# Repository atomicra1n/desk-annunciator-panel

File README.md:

# Desk Annunciator Panel

A smaller version of alarm panels found in Main Control Rooms of Nuclear Power Plants. Has 12 backlit alarm tiles, a seven segment display (8 digits) and ACK, RESET and TEST buttons. It is controlled by a Raspberry Pi Pico WH and shows live radiation readings from my [Wi-Fi Geiger Counter](https://github.com/atomicra1n/wifi-geiger-counter) which I made in Week 1 of Half Life. The alarm tiles light up when a problem occurs to notify me and play a sound.

## Features

- 12 alarm tiles with LEDs of three colors, red for critical alerts, yellow for warnings and white for reminders and general info.
- Proper annunciator sequence, new alarm flashes fast and creates sound, ACK makes the flashing steady and when condition is cleared it flashes slowly until RESET is pressed after which it stops being lit.
- TEST button lights up all tiles
- Seven segment display with 8 digits showing CPM and radiation levels in microSieverts/h from my Geiger project
- Demo mode for simulating alarms
- Fully through-hole with no SMD soldering and no screws needed for the enclosure

## Motivation

I've always loved nuclear energy and worked on many projects related to it. Annunciators are a particularly cool part of each NPP MCR and I thought having one at home would be really cool. Perhaps I can add a SCRAM button one day!

## Functionality

- The RPi Pico WH connects to Wi-Fi and checks the Geiger Counter's /api/data endpoint every 5 seconds to get the CPM, uSv/h, voltage status, counts and Wi-Fi signal
- Two shift registers drive the 12 tile LEDs. They run at 3.3V, and turn on yellow and red LEDs with a LOW output.
- White LEDs need 2.9V which is too close to 3.3V to work well, so they run from 5V via 2N3904 transistors. This means their logic is flipped.
- The MAX7219 display module needs 3.5V for a HIGH logic, yet our RPi only outputs 3.3V, so I made level shifters from three 2N3904 transistors. The signal is inverted, so the firmware must also send it inverted.
- The speaker is driven by another 2N3904 with a 47 ohm resistor and a flyback diode.
- Buttons go straight to the RPi Pico.

### Tiles

Red tiles: RAD HIGH, RAD HI-HI, HV FAULT, TUBE FAIL
Yellow tiles: RATE RISE, COMM LOST, WIFI WEAK, API ERROR
White tiles: WK REVIEWS, WK LESSONS, ANKI DUE, RAIN TODAY

I study Japanese and use many services to learn Kanji, vocabulary and grammar every day. As such, for the white tiles, I added tiles to notify me when I need to do some work on these services (WaniKani and Anki). However, as it would be a bit trickier to test, I only laid the foundation in the firmware for now and will add a proper API via a CF worker during build week.

## How it was made

I made the PCB itself in KiCad and used Fusion for the enclosure, a couple issues that arised:

- I originally wanted the 74HCT595 shift register so it could run at 5V and still take 3.3 volt logic, but GM Electronic (my local supplier) only had the SMD version, so instead I used the HC version at 3.3V. This meant I'd need to put the white LEDs on 5V.
- I initially put the white LEDs on 5 volts directly but realized the shift register outputs could end up above their 3.3V supply which the datasheet discourages, so I added transistors for the white LED row.
- Different shops listed the MAX display module anywhere between 80 and 85 milimeters long and nobody published the exact header hole locations, so I made a 3D printed support post that can be adjusted and printed again.
- The PCB is quite small for all it contains, so most of the logic goes on the back and the LEDs and speaker and seven segment went on the front.
- KiCad, just like always, assigned wrong footprints, so I needed to manually reassign
- My speaker needed a custom footprint as KiCad didn't have it built in.
- I accidentally inverted the LED logic when making the firmware, noticed it only as I was writing the journal entry!

## Tech stack

- KiCad for all PCB work
- Autodesk Fusion for the enclosure
- CircuitPython + Adafruit_requests library for the firmware

## Repo layout

- pcb/ has the KiCad project
- pcb/gerbers has all gerber and drill files + a zip for them
- cad has the .f3d file for Fusion and a .step file
- stl has the exported printable parts
- firmware/ contains the CircuitPython firmware and firmware/lib/ has the needed libraries (adafruit requests)
- images/ contains renders, screenshots and the printable label sheet

## Bill of materials

| Part | Qty | Source | Unit | Total |
|---|---|---|---|---|
| [PCB Manufacturing](https://jlcpcb.com) | 1 | JLCPCB | $4.00 | $4.00 |
| [CONNFLY BL120G-V8.5 female header 1x20pin](https://www.gme.cz/v/1498892/connfly-bl120g-v85-dutinkova-lista-1x20pin-roztec-254mm-vyska-85mm) | 3 | GM Electronic | $0.45 | $1.35 |
| [LED display seven segment MAX7219](https://www.gme.cz/v/1508913/led-displej-8x7-segmentu-cerveny) | 1 | GM Electronic | $3.57 | $3.57 |
| [Texas Instruments SN74HC595N](https://www.gme.cz/v/1490931/texas-instruments-sn74hc595n-cmos-8bit-posuvny-registr-se-seriovym-vstupem-s-vystupnym-registrem) | 2 | GM Electronic | $1.71 | $3.42 |
| [KLS DIL16PZ socket](https://www.gme.cz/v/1499942/kls-dil16pz-patice) | 2 | GM Electronic | $0.57 | $1.14 |
| [Lucky Light red LED 5 mm](https://www.gme.cz/v/1495977/lucky-light-503vd2e-v1-4i-led-5mm-cervena) | 4 | GM Electronic | $0.14 | $0.56 |
| [Lucky Light yellow LED 5 mm](https://www.gme.cz/v/1496003/lucky-light-503uyd2e-y2-4g-led-5mm-zluta) | 4 | GM Electronic | $0.17 | $0.68 |
| [OptoSupply white LED 5 mm](https://www.gme.cz/v/1491945/optosupply-osw5dk6ee2a-led-5mm-studena-bila) | 4 | GM Electronic | $0.36 | $1.44 |
| [Resistor 270 ohm 0207](https://www.gme.cz/v/1488130/gym-cym-rm-270r-06w-1-0207-metalizovany-rezistor) | 10 | GM Electronic | $0.10 | $1.00 |
| [Resistor 330 ohm 0207](https://www.gme.cz/v/1494116/gym-cym-rm-330r-06w-1-0207-metalizovany-rezistor) | 10 | GM Electronic | $0.10 | $1.00 |
| [Resistor 47 ohm 0207](https://www.gme.cz/v/1493086/gym-cym-rm-47r-06w-1-0207-metalizovany-rezistor) | 10 | GM Electronic | $0.10 | $1.00 |
| [Resistor 1 kiloohm 0207](https://www.gme.cz/v/1486228/gym-cym-rm-1k-06w-1-0207-metalizovany-rezistor) | 10 | GM Electronic | $0.10 | $1.00 |
| [Resistor 10 kiloohm 0207](https://www.gme.cz/v/1494150/gym-cym-rm-10k-06w-1-0207-metalizovany-rezistor) | 10 | GM Electronic | $0.10 | $1.00 |
| [SEMTECH 2N3904 transistor](https://www.gme.cz/v/1487027/semtech-2n3904-bipolarni-tranzistor) | 18 | GM Electronic | $0.06 | $1.08 |
| [SEMTECH 1N4148 diode](https://www.gme.cz/v/1487018/semtech-1n4148-dioda) | 19 | GM Electronic | $0.04 | $0.76 |
| [HITANO CK 100n/50V](https://www.gme.cz/v/1489676/hitano-ck-100n-50v-x7r-rm508-10-keramicky-kondenzator) | 3 | GM Electronic | $0.25 | $0.75 |
| [HITANO CE 47u/16V](https://www.gme.cz/v/1489745/hitano-ce-47u-16vt-hit-emr-5x7-rm2-bulk-elektrolyticky-kondenzator) | 16 | GM Electronic | $0.05 | $0.80 |
| [Kingstate KSSG3108 speaker](https://www.gme.cz/v/1498669/kingstate-kssg3108-magnetodynamicky-menic) | 1 | GM Electronic | $2.36 | $2.36 |
| [Diptronic DTS62K switch](https://www.gme.cz/v/1501370/diptronic-dts62k-mikrospinac) | 3 | GM Electronic | $0.25 | $0.75 |
| **Parts subtotal** | | | | **$27.66** |
| Shipping (estimate) | | | | $10.00 |
| **Total** | | | | **$37.66** |

The RPi Pico WH isn't included as I already own it. The order quantities are higher than the PCB technically needs as GM Electronic has minimum order quantities. 3D Printed parts will be printed by me at school. The total exceeds tier 1 funding, so I will cover the rest myself.

## Assembly

1. Order the PCB from JLCPCB using the exported gerber files and order the parts from your preferred electronics retailer.
2. Solder the back parts first (DIP sockets, resistors, transistors, capacitors, diode)
3. Solder the RPi Pico sockets on the back, make sure the USB points to the right board edge.
4. Solder the front LEDs, display pins, speaker and buttons.
5. Put the 74HC595 shift registers into their sockets and plug in the pico.
6. Flash CircuitPython to the pico.
7. Solder the straight header on the display module making sure the pins point out the back. The support post's pin should be in the module's corner hole. Plug the module into the pins.
8. Print the bezel face down, the back cover plate down and diffusers in white PLA.
9. Print the label sheet at 100% scale. Cut the labels out and secure them in the bezel cells.
10. Put the 3 button plungers into button holes from the inside.
11. Slide the PCB into the bezel until it is on the ledges, resting. Push the back cover in until a click is heard.

## Firmware

1. Download CircuitPython for the RPi Pico WH
2. Hold BOOTSEL on the Pico, plug it in and drag the downloaded .uf2 onto it.
3. When you see the CIRCUITPY drive, copy over code.py, tiles.py and the lib folder.
4. Rename settings.toml.example to settings.toml and fill it in, making sure you also put it on the CIRCUITPY drive.

## Controls

- ACK acknowledges flashing alarms and silences the alarm.
- RESET clears the alarms who's conditions have cleared.
- TEST lights up all tiles.

## AI disclosure

LLMs (Claude Opus 5.5) was used to get feedback on the PCB schematic and routing, review parts of the work and help find and fix bugs. It was also used for other tedious but simple tasks, such as adding the BOM to this README. AI was not used in writing the README, Journal or other parts of the project.

---

Built for [Hack Club Half Life](https://halflife.hackclub.com/) Week 4 (Displays).

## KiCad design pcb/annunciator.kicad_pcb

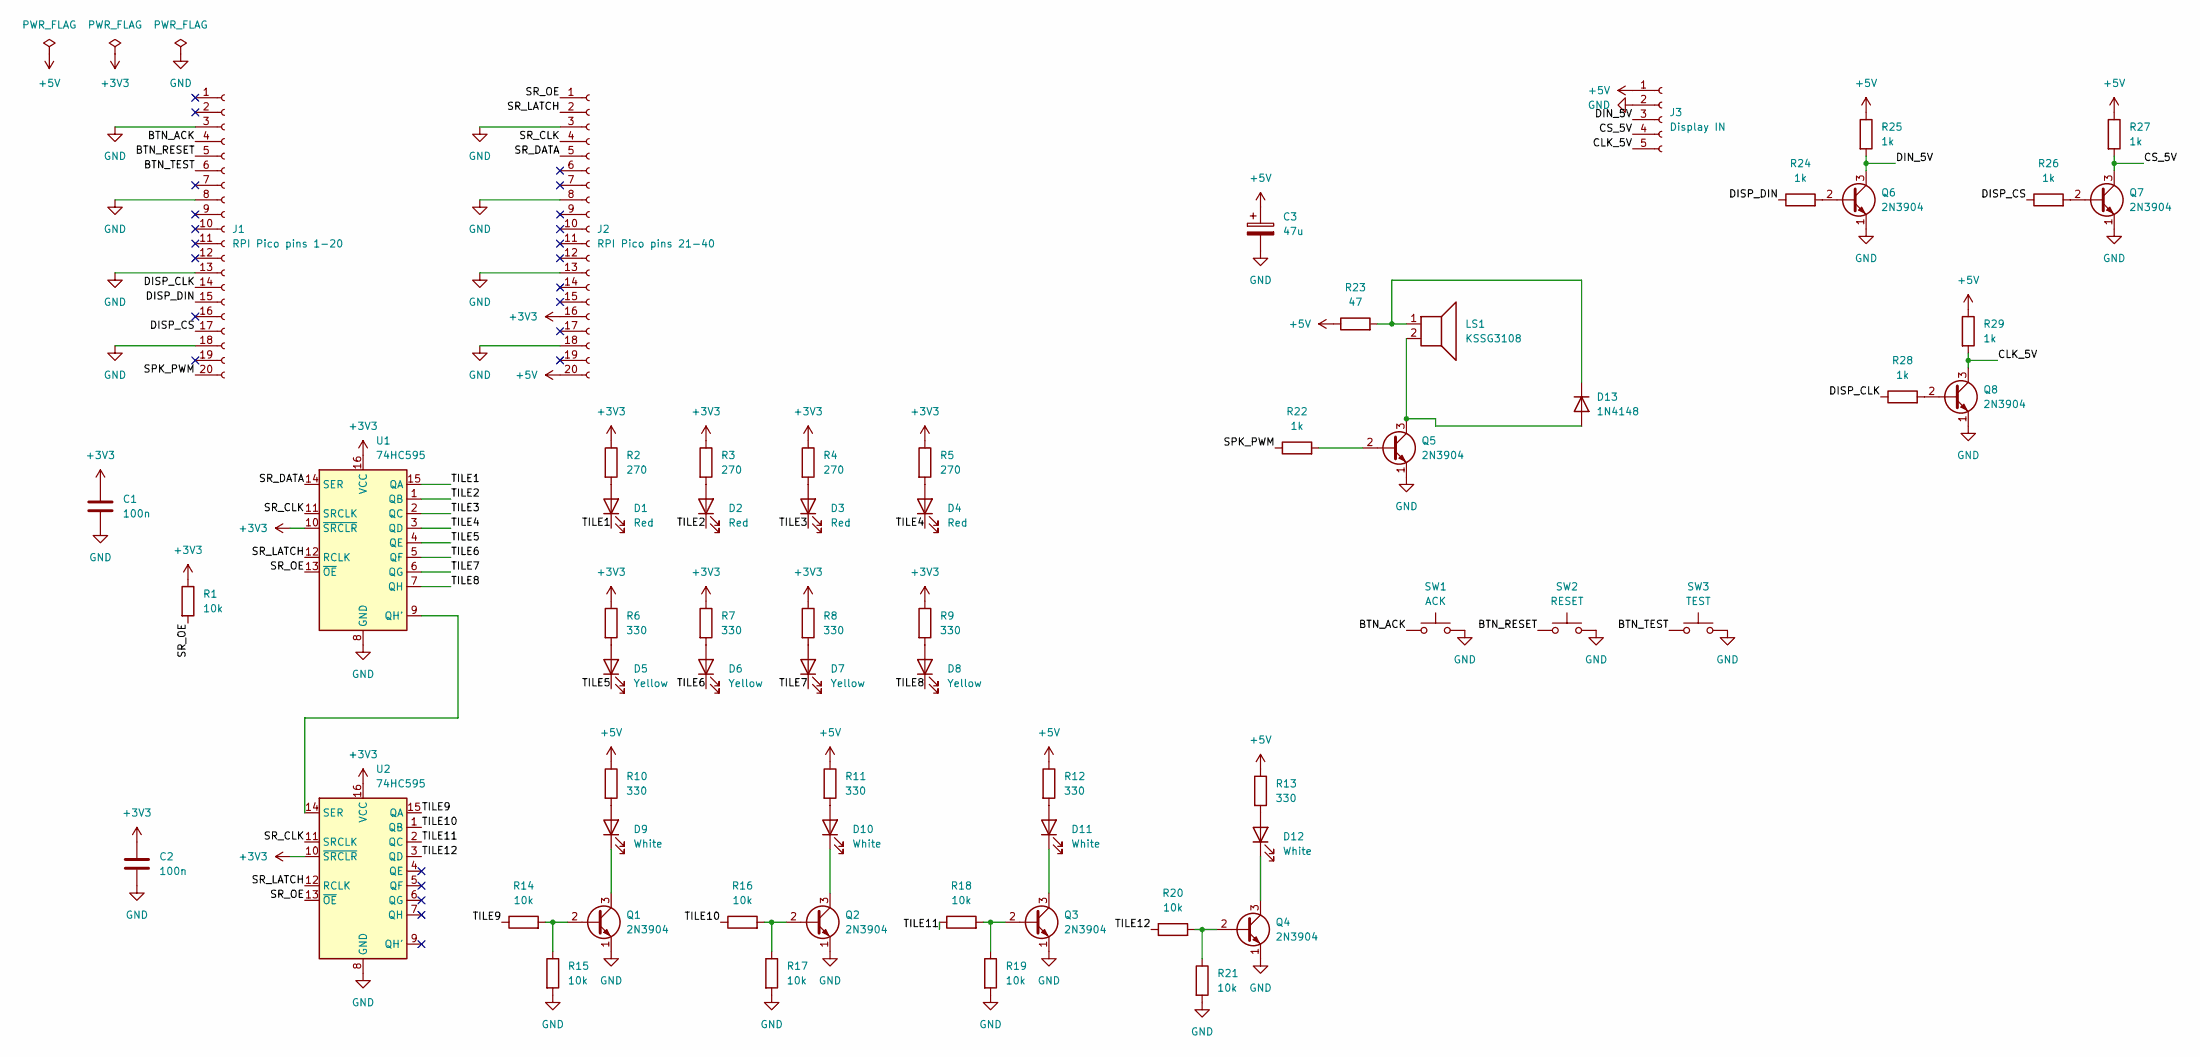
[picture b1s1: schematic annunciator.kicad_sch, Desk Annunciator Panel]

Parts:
C1, C2: 100n; C_Disc_D5.0mm_W2.5mm_P5.00mm
C3: 47u; CP_Radial_D5.0mm_P2.00mm
D1, D2, D3, D4: Red; LED_D5.0mm
D5, D6, D7, D8: Yellow; LED_D5.0mm
D9, D10, D11, D12: White; LED_D5.0mm
D13: 1N4148; D_DO-35_SOD27_P7.62mm_Horizontal
J1: RPI Pico pins 1-20; PinSocket_1x20_P2.54mm_Vertical
J2: RPI Pico pins 21-40; PinSocket_1x20_P2.54mm_Vertical
J3: Display IN; PinSocket_1x05_P2.54mm_Vertical
LS1: KSSG3108
Q1, Q2, Q3, Q4, Q5, Q6, Q7, Q8: 2N3904; TO-92_Inline
R1, R14, R15, R16, R17, R18, R19, R20, R21: 10k; R_Axial_DIN0207_L6.3mm_D2.5mm_P10.16mm_Horizontal
R2, R3, R4, R5: 270; R_Axial_DIN0207_L6.3mm_D2.5mm_P10.16mm_Horizontal
R6, R7, R8, R9, R10, R11, R12, R13: 330; R_Axial_DIN0207_L6.3mm_D2.5mm_P10.16mm_Horizontal
R22, R24, R25, R26, R27, R28, R29: 1k; R_Axial_DIN0207_L6.3mm_D2.5mm_P10.16mm_Horizontal
R23: 47; R_Axial_DIN0207_L6.3mm_D2.5mm_P10.16mm_Horizontal
SW1: ACK; SW_PUSH_6mm
SW2: RESET; SW_PUSH_6mm
SW3: TEST; SW_PUSH_6mm
U1, U2: 74HC595; DIP-16_W7.62mm_Socket

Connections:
+3V3: C1.1, C2.1, J2.16, R1.1, R2.1, R3.1, R4.1, R5.1, R6.1, R7.1, R8.1, R9.1, U1.10 (~SRCLR), U1.16 (VCC), U2.10 (~SRCLR), U2.16 (VCC)
+5V: C3.1, J2.20, J3.1, R10.1, R11.1, R12.1, R13.1, R23.1, R25.1, R27.1, R29.1
/BTN_ACK: J1.4, SW1.1
/BTN_RESET: J1.5, SW2.1
/BTN_TEST: J1.6, SW3.1
/CLK_5V: J3.5, Q8.3 (C), R29.2
/CS_5V: J3.4, Q7.3 (C), R27.2
/DIN_5V: J3.3, Q6.3 (C), R25.2
/DISP_CLK: J1.14, R28.1
/DISP_CS: J1.17, R26.1
/DISP_DIN: J1.15, R24.1
/SPK_PWM: J1.20, R22.1
/SR_CLK: J2.4, U1.11 (SRCLK), U2.11 (SRCLK)
/SR_DATA: J2.5, U1.14 (SER)
/SR_LATCH: J2.2, U1.12 (RCLK), U2.12 (RCLK)
/SR_OE: J2.1, R1.2, U1.13 (~OE), U2.13 (~OE)
/TILE1: D1.1 (K), U1.15 (QA)
/TILE2: D2.1 (K), U1.1 (QB)
/TILE3: D3.1 (K), U1.2 (QC)
/TILE4: D4.1 (K), U1.3 (QD)
/TILE5: D5.1 (K), U1.4 (QE)
/TILE6: D6.1 (K), U1.5 (QF)
/TILE7: D7.1 (K), U1.6 (QG)
/TILE8: D8.1 (K), U1.7 (QH)
/TILE9: R14.1, U2.15 (QA)
/TILE10: R16.1, U2.1 (QB)
/TILE11: R18.1, U2.2 (QC)
/TILE12: R20.1, U2.3 (QD)
GND: C1.2, C2.2, C3.2, J1.3, J1.8, J1.13, J1.18, J2.3, J2.8, J2.13, J2.18, J3.2, Q1.1 (E), Q2.1 (E), Q3.1 (E), Q4.1 (E), Q5.1 (E), Q6.1 (E), Q7.1 (E), Q8.1 (E), R15.2, R17.2, R19.2, R21.2, SW1.2, SW2.2, SW3.2, U1.8 (GND), U2.8 (GND)
unnamed: D1.2 (A), R2.2
unnamed: D2.2 (A), R3.2
unnamed: D3.2 (A), R4.2
unnamed: D4.2 (A), R5.2
unnamed: D5.2 (A), R6.2
unnamed: D6.2 (A), R7.2
unnamed: D7.2 (A), R8.2
unnamed: D8.2 (A), R9.2
unnamed: D9.2 (A), R10.2
unnamed: D9.1 (K), Q1.3 (C)
unnamed: D10.2 (A), R11.2
unnamed: D10.1 (K), Q2.3 (C)
unnamed: D11.2 (A), R12.2
unnamed: D11.1 (K), Q3.3 (C)
unnamed: D12.2 (A), R13.2
unnamed: D12.1 (K), Q4.3 (C)
unnamed: D13.2 (A), LS1.2, Q5.3 (C)
unnamed: D13.1 (K), LS1.1, R23.2
unnamed: Q1.2 (B), R14.2, R15.1
unnamed: Q2.2 (B), R16.2, R17.1
unnamed: Q3.2 (B), R18.2, R19.1
unnamed: Q4.2 (B), R20.2, R21.1
unnamed: Q5.2 (B), R22.2
unnamed: Q6.2 (B), R24.2
unnamed: Q7.2 (B), R26.2
unnamed: Q8.2 (B), R28.2
unnamed: U1.9 (QH'), U2.14 (SER)

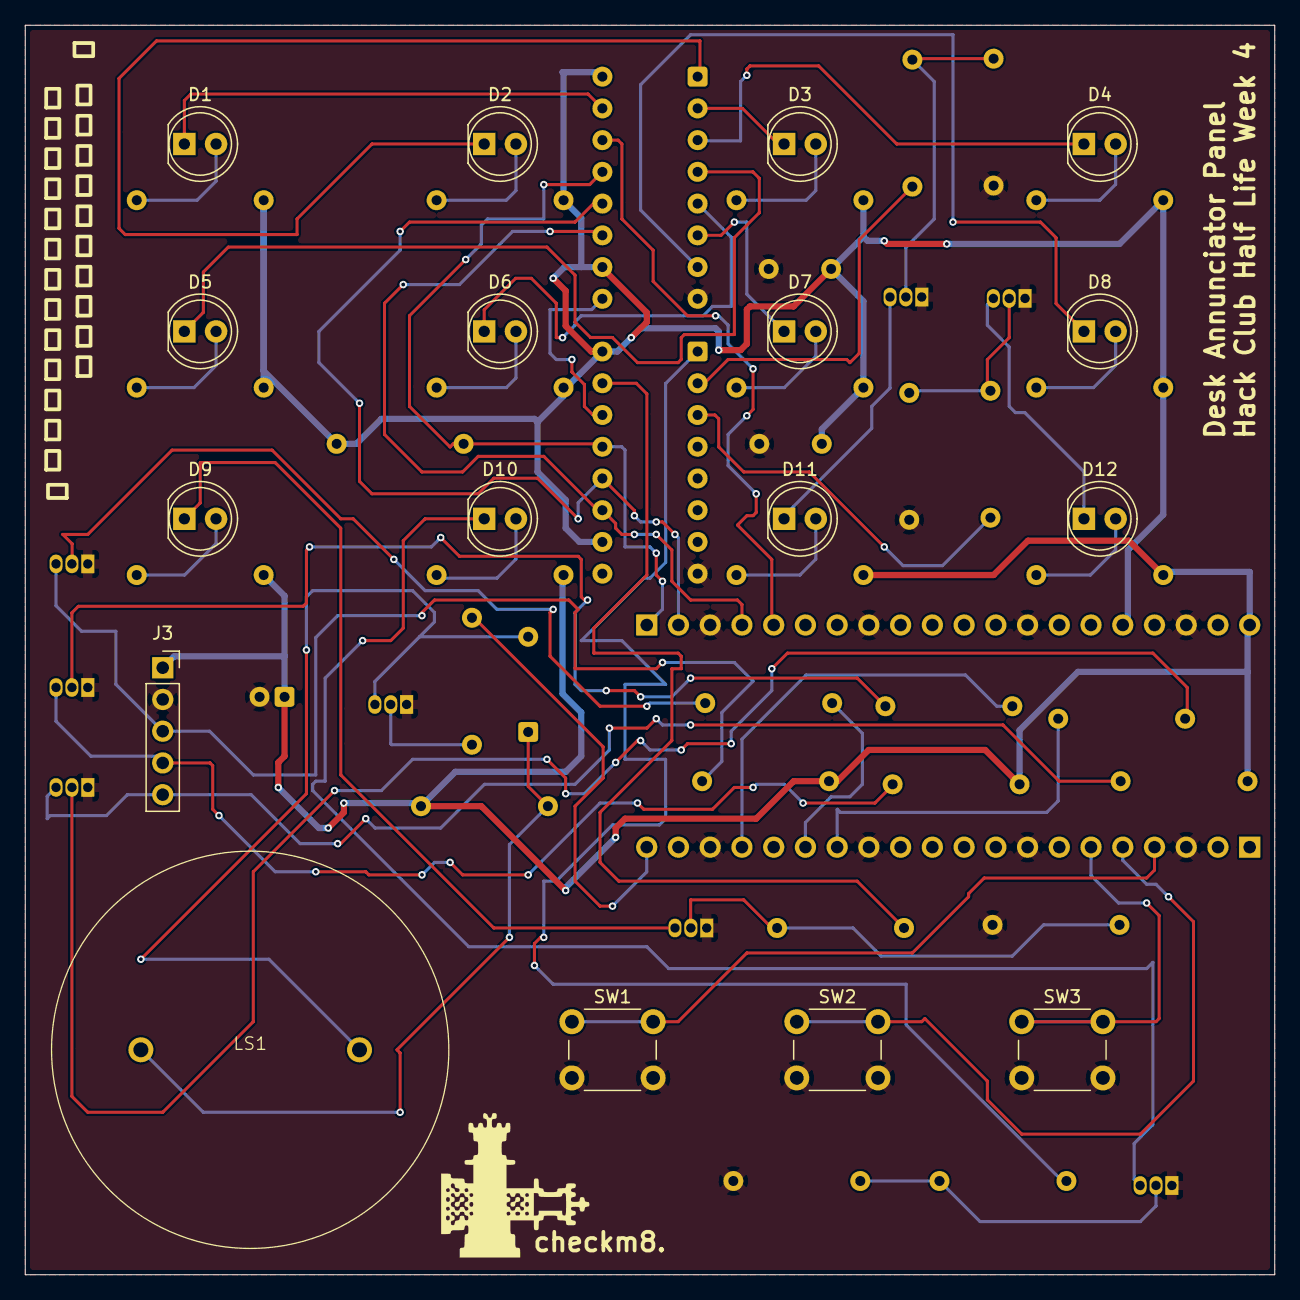
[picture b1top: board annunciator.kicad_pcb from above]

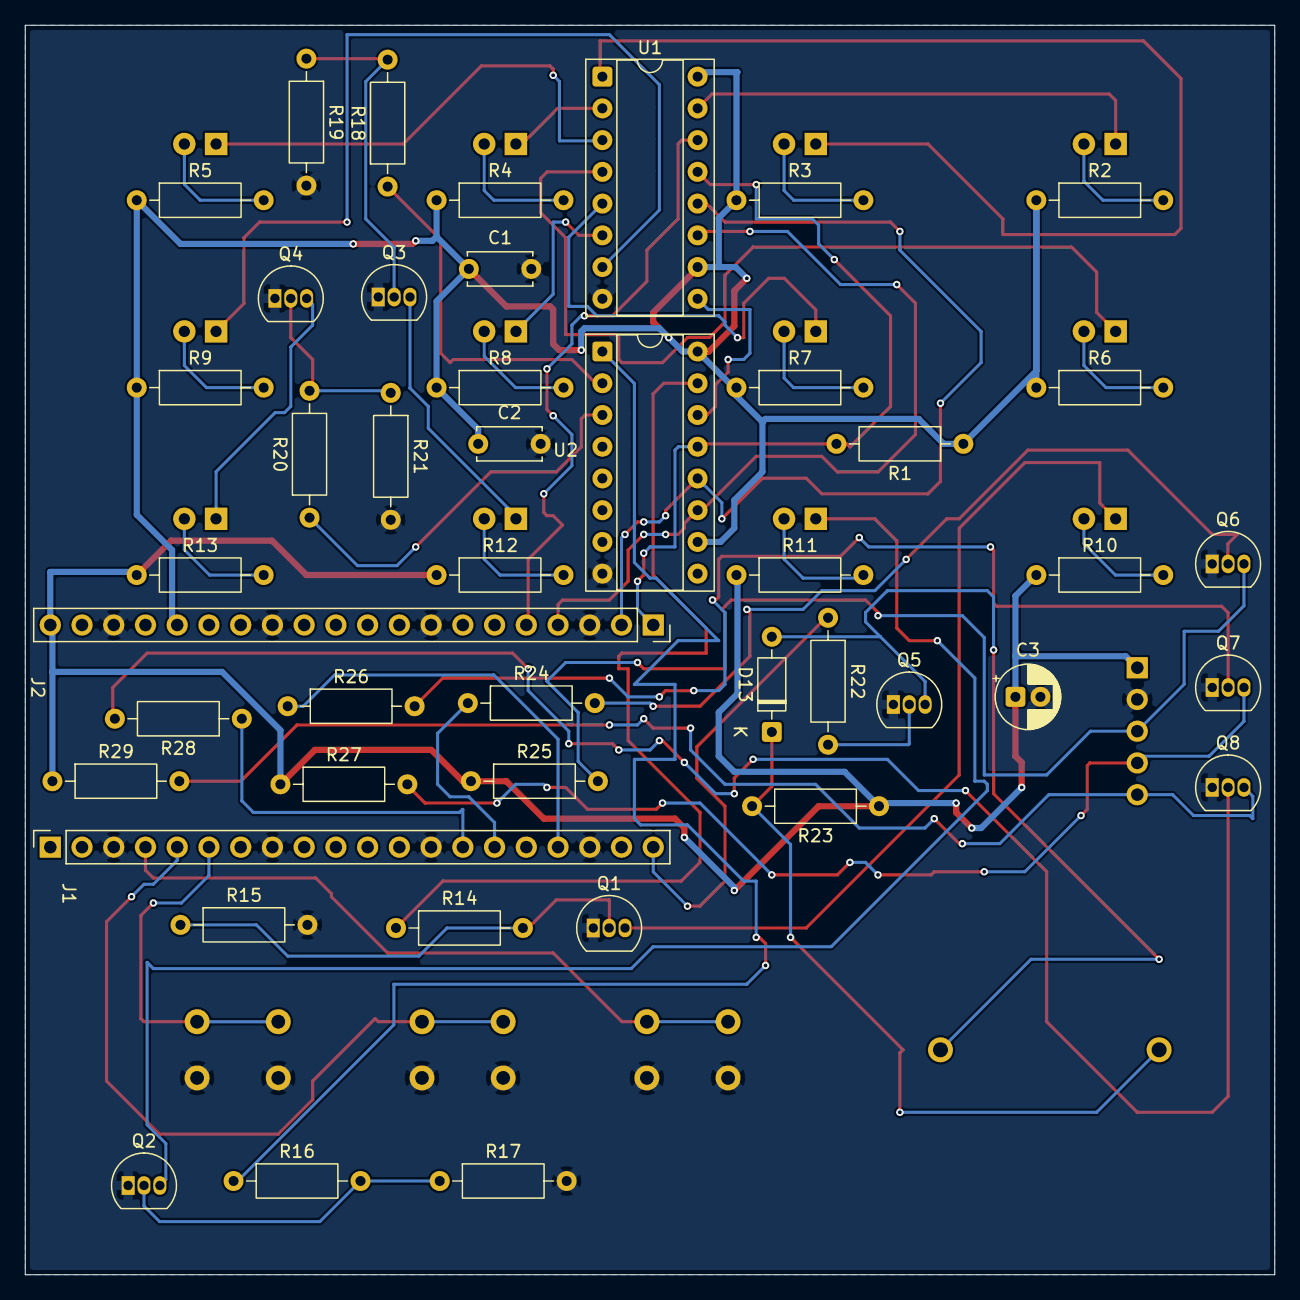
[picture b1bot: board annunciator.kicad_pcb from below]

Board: 2 copper layers, 100.0 x 100.0 mm, 62 parts (45 on the bottom side), 56 nets.
